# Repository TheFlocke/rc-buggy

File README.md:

# RC Rover 🌋 (WIP)

This project was developed as part of a high school competition organized by the German Aerospace Center (DLR). The challenge: design and build a rover capable of:
- 📊 Collecting sensor data
- 🧭 Navigating autonomously
- 🦾 Using a robotic arm to gather rock samples

To enable wireless control from any BLE-capable device, I developed:
- 💻 Custom microcontroller software
- 🌐 Dedicated web app
- 🖥️ Bespoke PCB design (unfortunately, the PCB was never manufactured due to supply issues)

The foundation for the code was a project from my teacher, which I significantly modified and expanded. While I focused on electronics/software ⚡️, my teammates handled mechanical engineering ⚙️.

## Project Screenshots 📸

## Installation ⚙️
### 🔌 Flash mcu-sw onto the ESP32
#### 1. 📋 Install Prerequisites
You’ll need VS Code or CLion with the PlatformIO extension.  
See the Links section below for tutorials.

#### 2. 💾 Download the Project
Clone or download this repository and open it in your chosen IDE.

#### 3. 🆔 Generate New UUIDs
1. Open `ESP32ble.h`  
2. Visit [uuidgenerator.net](https://www.uuidgenerator.net/)  
3. Generate new UUIDs and replace existing ones

#### 4. ⚡ Flash the ESP32
Upload the code to your ESP32 device.

#### 5. 📶 Test BLE Communication
Use nRF Connect or similar BLE apps to verify data transmission.

## Acknowledgements 🙏
- 👨‍🏫 [RC Car Project by my Teacher](https://github.com/bkZuendorf/rc-car)
- 🖨️ [3D-Printable Parts Repository](https://github.com/matiassingers/awesome-readme)

## Authors 👥
- [@TheFlocke](https://github.com/TheFlocke) 👤
- [@xNiicki](https://github.com/xNiicki) 👤

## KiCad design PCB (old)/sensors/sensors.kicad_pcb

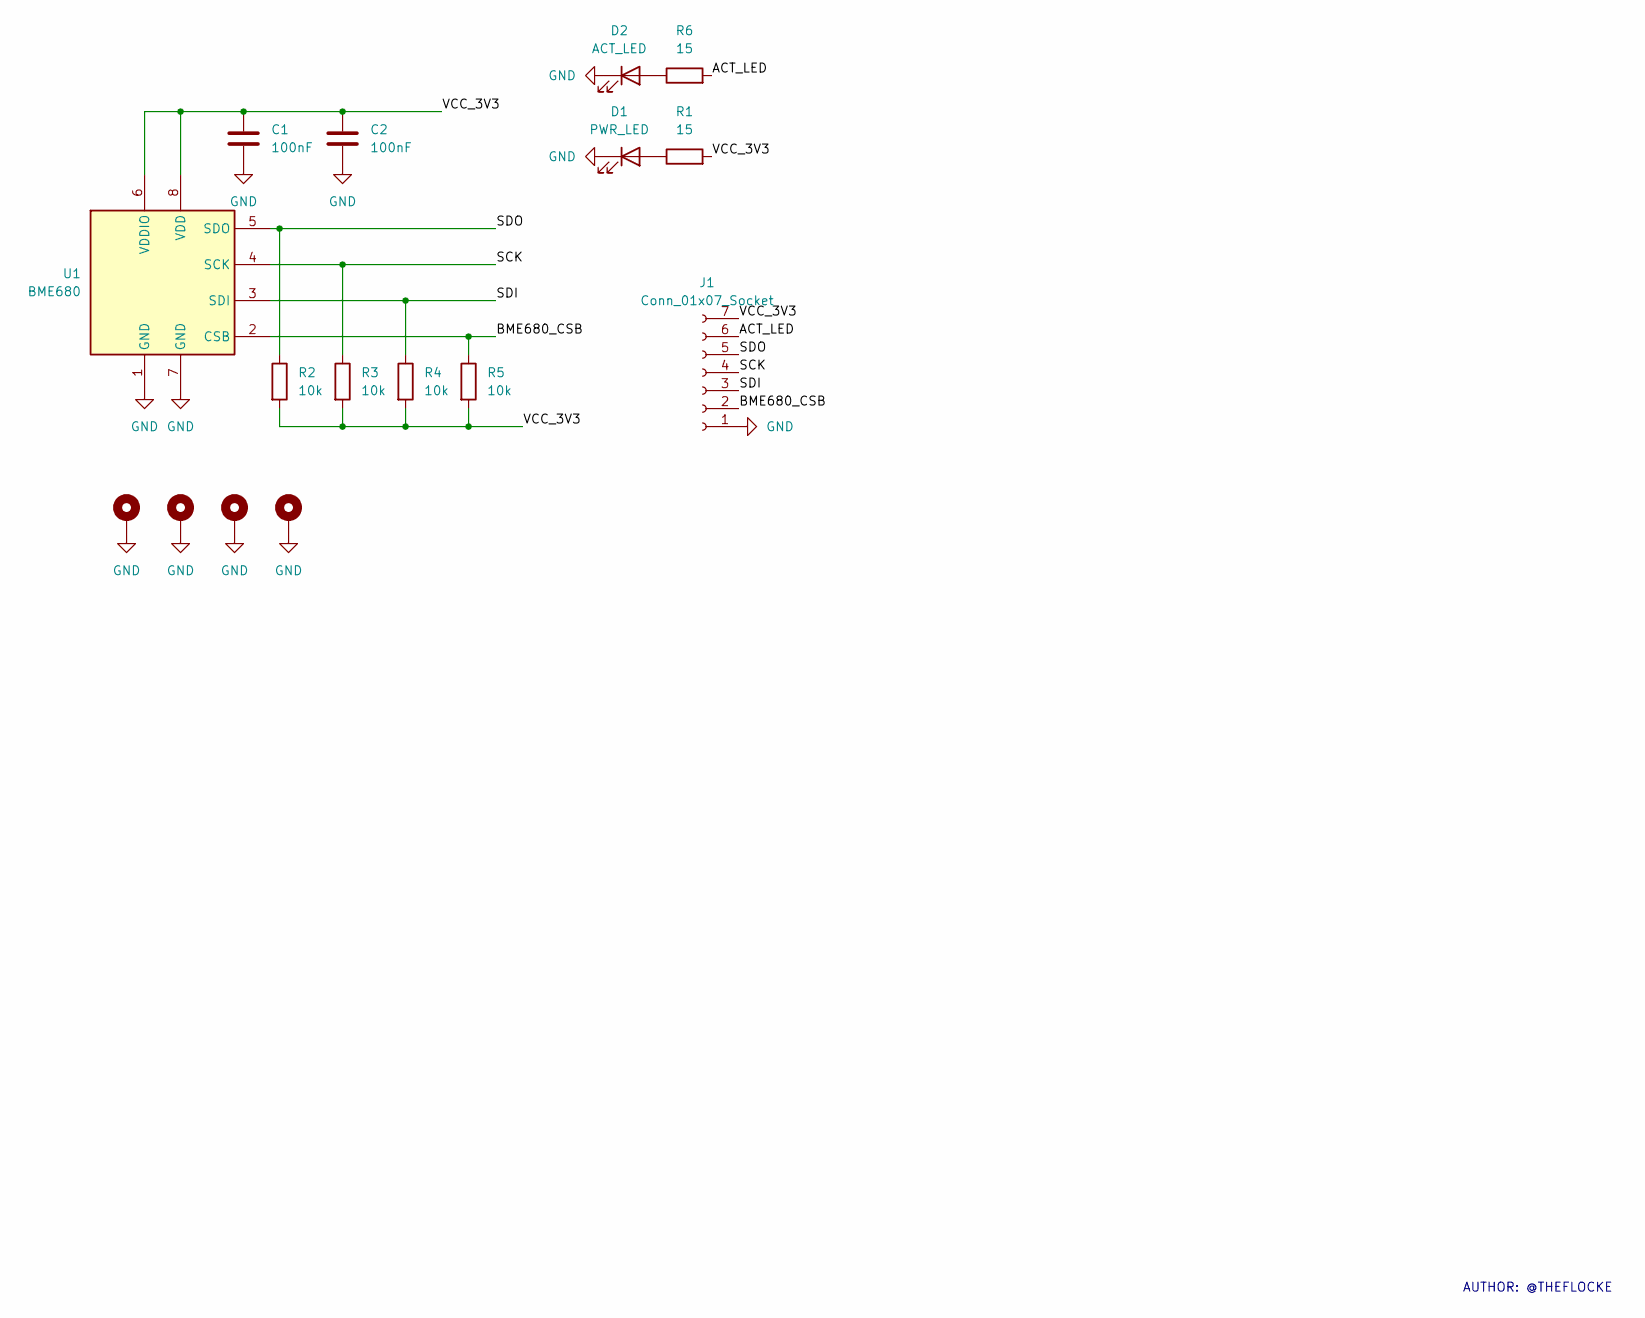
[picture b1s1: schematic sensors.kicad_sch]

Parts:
C1, C2: 100nF; C_0805_2012Metric_Pad1.18x1.45mm_HandSolder
D1: PWR_LED; C_0805_2012Metric_Pad1.18x1.45mm_HandSolder
D2: ACT_LED; C_0805_2012Metric_Pad1.18x1.45mm_HandSolder
H1, H2, H3, H4: MountingHole_Pad; MountingHole_3.2mm_M3_DIN965_Pad_TopBottom
J1: Conn_01x07_Socket; JST_EH_B7B-EH-A_1x07_P2.50mm_Vertical
R1, R6: 15; R_0805_2012Metric_Pad1.20x1.40mm_HandSolder
R2, R3, R4, R5: 10k; R_0805_2012Metric_Pad1.20x1.40mm_HandSolder
U1: BME680; Bosch_LGA-8_3x3mm_P0.8mm_ClockwisePinNumbering

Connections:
/ACT_LED: J1.6, R6.2
/BME680_CSB: J1.2, R5.1, U1.2 (CSB)
/SCK: J1.4, R3.1, U1.4 (SCK)
/SDI: J1.3, R4.1, U1.3 (SDI)
/SDO: J1.5, R2.1, U1.5 (SDO)
/VCC_3V3: C1.1, C2.1, J1.7, R1.2, R2.2, R3.2, R4.2, R5.2, U1.6 (VDDIO), U1.8 (VDD)
GND: C1.2, C2.2, D1.1 (K), D2.1 (K), H1.1, H2.1, H3.1, H4.1, J1.1, U1.1 (GND), U1.7 (GND)
unnamed: D1.2 (A), R1.1
unnamed: D2.2 (A), R6.1

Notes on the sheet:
AUTHOR: @THEFLOCKE

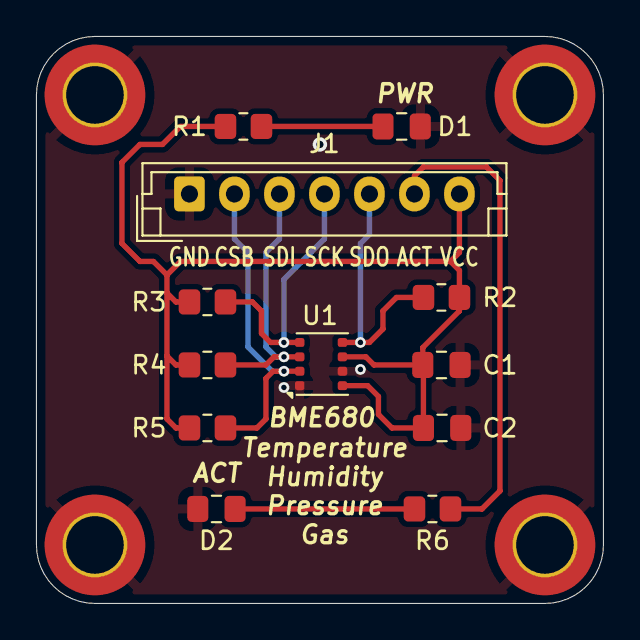
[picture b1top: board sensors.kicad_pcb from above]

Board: 2 copper layers, 31.5 x 31.5 mm, 16 parts (0 on the bottom side), 9 nets.

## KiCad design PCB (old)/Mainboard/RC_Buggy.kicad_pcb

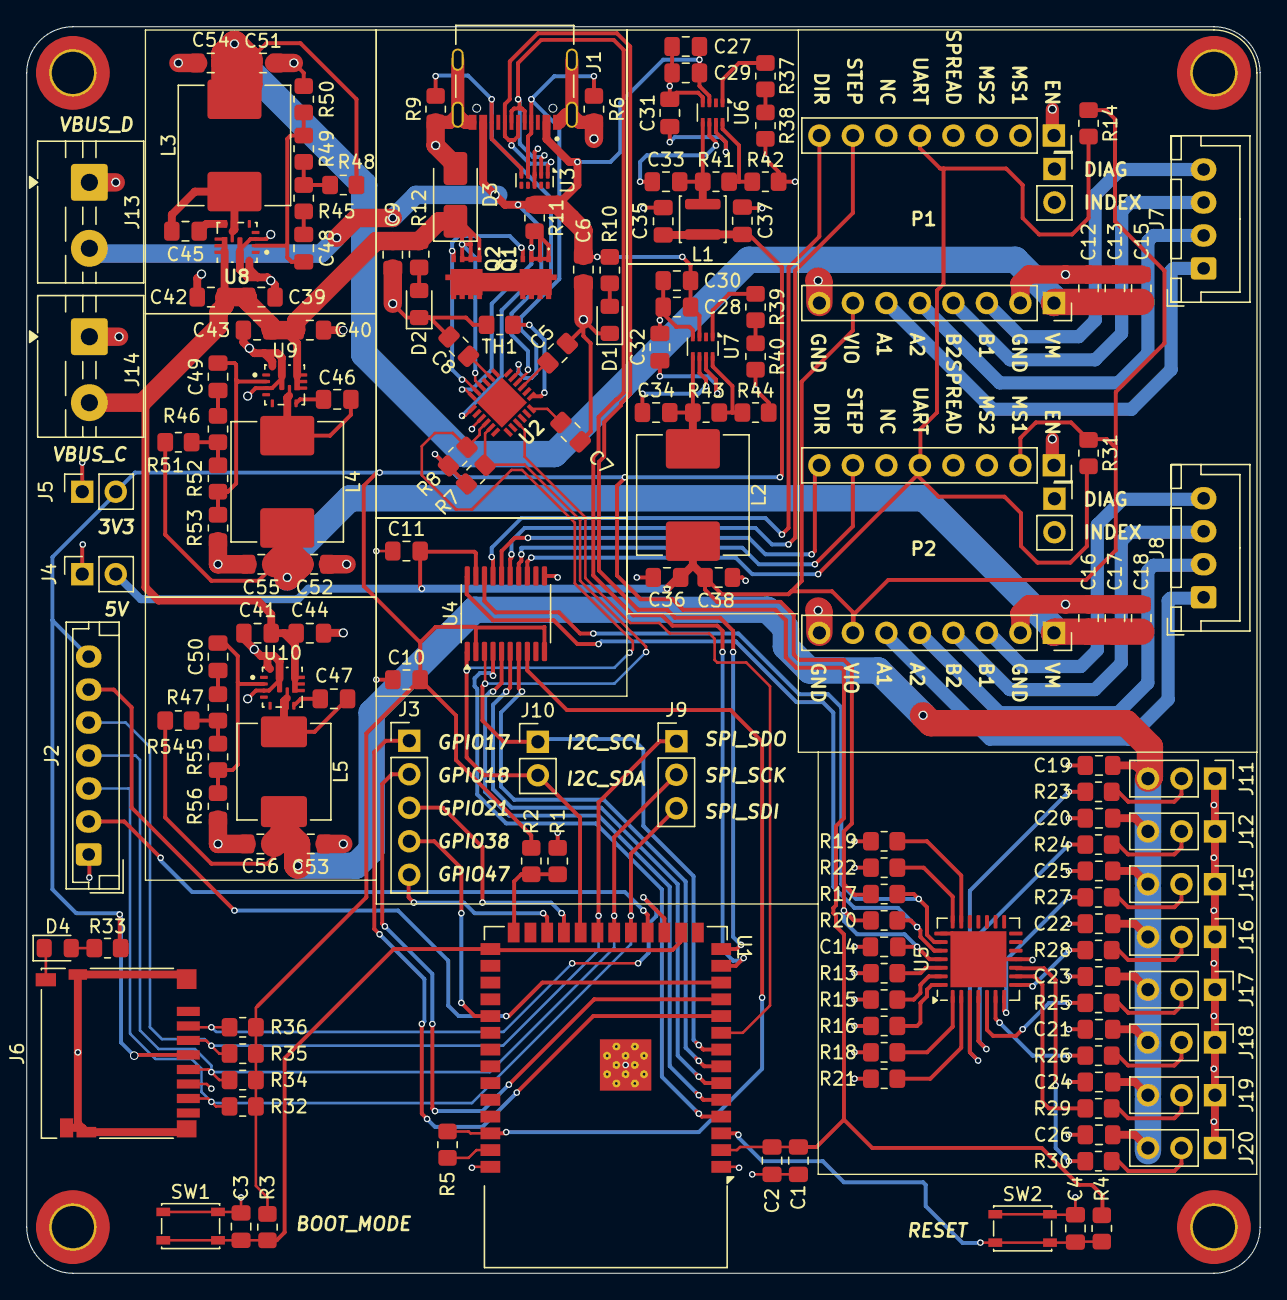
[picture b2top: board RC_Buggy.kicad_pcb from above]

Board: 4 copper layers, 93.5 x 94.5 mm, 162 parts (0 on the bottom side), 111 nets.

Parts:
C1, C3, C4, C10, C11, C45, C46, C47: 0u1F; C_0805_2012Metric_Pad1.18x1.45mm_HandSolder
C2, C6, C9, C14, C27, C28, C29, C30, C39, C40, C41, C42, C43, C44: 10uF; C_0805_2012Metric_Pad1.18x1.45mm_HandSolder
C5, C7, C13, C15, C17, C18, C19, C20, C21, C22, C23, C24, C25, C26, C33, C34: 100nF; C_0805_2012Metric_Pad1.18x1.45mm_HandSolder
C8: 1uF; C_0805_2012Metric_Pad1.18x1.45mm_HandSolder
C12, C16: 100uF; C_0805_2012Metric_Pad1.18x1.45mm_HandSolder
C31, C32: 33nF; C_0805_2012Metric_Pad1.18x1.45mm_HandSolder
C35, C36, C37, C38, C51, C52, C53, C54, C55, C56: 22uF; C_0805_2012Metric_Pad1.18x1.45mm_HandSolder
C48, C49, C50: 100pF; C_0805_2012Metric_Pad1.18x1.45mm_HandSolder
D1, D2, D4: LED; D_0805_2012Metric_Pad1.15x1.40mm_HandSolder
D3: 100V; D_SMA
H1, H2, H3, H4: MountingHole_Pad; MountingHole_3.2mm_M3_DIN965_Pad_TopBottom
J1: TYPE-C-31-M-12; HRO_TYPE-C-31-M-12
J2: BME680; JST_EH_B7B-EH-A_1x07_P2.50mm_Vertical
J3: GPIO; PinHeader_1x05_P2.54mm_Vertical
J4: PW_5V; PinSocket_1x02_P2.54mm_Vertical
J5: PW_3V3; PinSocket_1x02_P2.54mm_Vertical
J6: Micro_SD_Card_Det_Hirose_DM3AT; microSD_HC_Hirose_DM3D-SF
J7: Stepper_1; JST_XH_B4B-XH-A_1x04_P2.50mm_Vertical
J8: Stepper_2; JST_XH_B4B-XH-A_1x04_P2.50mm_Vertical
J9: SPI; PinHeader_1x03_P2.54mm_Vertical
J10: I2C; PinHeader_1x02_P2.54mm_Vertical
J11: Servo 0; PinHeader_1x03_P2.54mm_Vertical
J12: Servo 1; PinHeader_1x03_P2.54mm_Vertical
J13, J14: PW_IO_bak; TerminalBlock_MaiXu_MX126-5.0-02P_1x02_P5.00mm
J15: Servo 4; PinHeader_1x03_P2.54mm_Vertical
J16: Servo 5; PinHeader_1x03_P2.54mm_Vertical
J17: Servo 2; PinHeader_1x03_P2.54mm_Vertical
J18: Servo 3; PinHeader_1x03_P2.54mm_Vertical
J19: Servo 6; PinHeader_1x03_P2.54mm_Vertical
J20: Servo 7; PinHeader_1x03_P2.54mm_Vertical
L1: 2u4H; L_APV_ANR3015
L2, L3, L4: 3u3H; L_APV_APH0850
L5: 4u3H; L_APV_APH0650
P1, P2: TMC2209_Socket
Q1, Q2: AON7262E
R1, R2, R3, R4, R10, R12, R13, R14, R15, R16, R17, R18, R19, R20, R21, R22, R31, R32, R34, R35, R36, R37, R38, R39, R40, R42, R44, R50, R53, R56: 10k; R_0805_2012Metric_Pad1.20x1.40mm_HandSolder
R5: 1k; R_0805_2012Metric_Pad1.20x1.40mm_HandSolder
R6, R7, R8, R9: 5k1; R_0805_2012Metric_Pad1.20x1.40mm_HandSolder
R11: 10m; R_0805_2012Metric_Pad1.20x1.40mm_HandSolder
R23, R24, R25, R26, R27, R28, R29, R30: 220; R_0805_2012Metric_Pad1.20x1.40mm_HandSolder
R33: 15; R_0805_2012Metric_Pad1.20x1.40mm_HandSolder
R41: 31k6; R_0805_2012Metric_Pad1.20x1.40mm_HandSolder
R43: 52k3; R_0805_2012Metric_Pad1.20x1.40mm_HandSolder
R45, R46, R47: 20k; R_0805_2012Metric_Pad1.20x1.40mm_HandSolder
R48, R51, R54: 49k9; R_0805_2012Metric_Pad1.20x1.40mm_HandSolder
R49, R52: 73k2; R_0805_2012Metric_Pad1.20x1.40mm_HandSolder
R55: 100k; R_0805_2012Metric_Pad1.20x1.40mm_HandSolder
SW1, SW2: SW_Push; SW_SPST_PTS810
TH1: NTC-10k; R_0805_2012Metric_Pad1.20x1.40mm_HandSolder
U1: ESP32-S3-WROOM-1
U2: AP33772
U3: TPD4E05U06DQA; USON-10_2.5x1.0mm_P0.5mm
U4: TXS0108EPW; TSSOP-20_4.4x6.5mm_P0.65mm
U5: PCA9685BS; QFN-28-1EP_6x6mm_P0.65mm_EP4.25x4.25mm
U6, U7: TPS62933; SOT-583-8
U8, U9, U10: TPS56637RPAR; CONV_TPS56637RPAR

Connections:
/ACT_LED: J2.6, U1.12 (IO8)
/BME680_CSB: J2.2, U1.18 (IO10)
/BOOT_Mode: C3.1, R3.2, SW1.2, U1.16 (IO46), U1.27 (IO0)
/CHIP_PU: C4.1, R4.2, SW2.2, U1.3 (EN)
/Connections/PWM0: J11.2, R23.2
/Connections/PWM1: J12.2, R24.2
/Connections/PWM2: J17.2, R25.2
/Connections/PWM3: J18.2, R26.2
/Connections/PWM4: J15.2, R27.2
/Connections/PWM5: J16.2, R28.2
/Connections/PWM6: J19.2, R29.2
/Connections/PWM7: J20.2, R30.2
/Connections/STEP1_A1: J7.1, P1.14 (B1)
/Connections/STEP1_A2: J7.2, P1.13 (A1)
/Connections/STEP1_B1: J7.4, P1.11 (B2)
/Connections/STEP1_B2: J7.3, P1.12 (A2)
/Connections/STEP2_A1: J8.1, P2.14 (B1)
/Connections/STEP2_A2: J8.2, P2.13 (A1)
/Connections/STEP2_B1: J8.4, P2.11 (B2)
/Connections/STEP2_B2: J8.3, P2.12 (A2)
/GPIO17: J3.1, U1.10 (IO17)
/GPIO18: J3.2, U1.11 (IO18)
/GPIO21: J3.3, U1.23 (IO21)
/GPIO38: J3.4, U1.31 (IO38)
/GPIO47: J3.5, U1.24 (IO47)
/I2C_SCL: J10.1, R7.1, U1.8 (IO15), U2.5 (SCL), U4.3 (A2)
/I2C_SDA: J10.2, R8.1, U1.22 (IO14), U2.4 (SDA), U4.1 (A1)
/Logic Level Converter/DATA0_5V: R20.1, U4.20 (B1), U5.24 (SDA)
/Logic Level Converter/DATA1_5V: R17.2, U4.18 (B2), U5.23 (SCL)
/Logic Level Converter/DATA2_5V: P1.8 (DIR), U4.17 (B3)
/Logic Level Converter/DATA3_5V: P2.8 (DIR), U4.16 (B4)
/Logic Level Converter/DATA4_5V: P1.7 (STEP), U4.15 (B5)
/Logic Level Converter/DATA5_5V: P2.7 (STEP), U4.14 (B6)
/Logic Level Converter/DATA6_5V: P1.5 (UART), P2.5 (UART), R14.2, R31.2, U4.13 (B7)
/PD_INT: U1.9 (IO16), U2.9 (GPIO3)
/SD_CSB: J6.2 (DAT3/CD), R36.1, U1.17 (IO9)
/SPI_SCK: J2.4, J6.5 (CLK), J9.2, R34.1, U1.20 (IO12)
/SPI_SDI: J2.3, J6.7 (DAT0), J9.3, R32.1, U1.19 (IO11)
/SPI_SDO: J2.5, J6.3 (CMD), J9.1, R35.1, U1.21 (IO13)
/STEP1_DIR: U1.4 (IO4), U4.4 (A3)
/STEP1_STEP: U1.6 (IO6), U4.6 (A5)
/STEP2_DIR: U1.5 (IO5), U4.5 (A4)
/STEP2_STEP: U1.7 (IO7), U4.7 (A6)
/UART_RX: R5.1, U1.38 (IO2), U4.8 (A7)
/UART_TX: R5.2, U1.39 (IO1)
/USB-C/CC1: J1.A5 (CC1), R6.2, U2.17 (CC1), U3.4 (D2+)
/USB-C/CC2: J1.B5 (CC2), R9.2, U2.16 (CC2), U3.5 (D2-)
/USB-C/PWR_EN: Q1.4 (G), Q2.4 (G), U2.23 (PWR_EN)
/USB-C/VCC: Q1.1 (S_1), Q1.2 (S_2), Q1.3 (S_3), R11.2, U2.24 (VCC)
/USB_D+: J1.A6 (DP1), J1.B6 (DP2), U1.14 (USB_D+), U3.1 (D1+)
/USB_D-: J1.A7 (DN1), J1.B7 (DN2), U1.13 (USB_D-), U3.2 (D1-)
GND: C1.2, C2.2, C3.2, C4.2, C5.2, C6.2, C7.2, C8.2, C9.2, C10.1, C11.1, C12.2, C13.1, C14.1, C15.1, C16.2, C17.1, C18.1, C19.2, C20.2, C21.2, C22.2, C23.2, C24.2, C25.2, C26.2, C27.2, C28.2, C29.2, C30.2, C31.2, C32.2, C35.2, C36.2, C37.2, C38.2, C39.2, C40.2, C41.2, C42.2, C43.2, C44.2, C51.2, C52.2, C53.2, C54.2, C55.2, C56.2, D1.1 (K), D2.1 (K), D3.2 (A), H1.1, H2.1, H3.1, H4.1, J1.A1_B12 (GND), J1.B1_A12 (GND), J1.S1 (SHIELD), J1.S2 (SHIELD), J1.S3 (SHIELD), J1.S4 (SHIELD), J2.1, J4.1, J5.1, J6.6 (VSS), J6.9 (DET_B), J6.11 (SHIELD), J11.1, J12.1, J13.1, J14.1, J15.1, J16.1, J17.1, J18.1, J19.1, J20.1, P1.1 (EN), P1.10 (GND), P1.16 (GND), P2.1 (EN), P2.10 (GND), P2.16 (GND), R1.2, R6.1, R9.1, R13.2, R15.2, R16.2, R18.2, R19.1, R21.2, R22.2, R38.2, R40.2, R42.2, R44.2, R50.2, R53.2, R56.2, SW1.1, SW2.1, TH1.2, U1.1 (GND), U1.40 (GND), U1.41 (GND), U2.3 (GND), U3.3 (GND), U3.8 (GND), U4.11 (GND), U5.11 (VSS), U5.22 (EXTCLK), U5.29 (VSS), U6.4 (GND), U7.4 (GND), U8.3 (AGND), U8.9 (PGND), U8.10 (MODE), U9.3 (AGND), U9.9 (PGND), U9.10 (MODE), U10.3 (AGND), U10.9 (PGND), U10.10 (MODE)
unnamed: C48.1, R45.1
unnamed: C49.1, R46.1
unnamed: C50.1, R47.1
unnamed: D1.2 (A), R10.1
unnamed: D2.2 (A), R12.1
unnamed: D4.2 (A), R33.1
unnamed: D4.1 (K), J6.10 (DET_A)
unnamed: Q1.5 (D_1), Q1.6 (D_2), Q1.7 (D_3), Q1.8 (D_4), Q1.9 (D_5), Q1.10 (D_6), Q1.11 (D_7), Q2.5 (D_1), Q2.6 (D_2), Q2.7 (D_3), Q2.8 (D_4), Q2.9 (D_5), Q2.10 (D_6), Q2.11 (D_7)
unnamed: R37.2, R38.1
unnamed: R39.2, R40.1
unnamed: R45.2, R48.2, R49.1
unnamed: R46.2, R51.2, R52.1
unnamed: R47.2, R54.2, R55.1
unnamed: R1.1, R2.1, U1.26 (IO45)
unnamed: C5.1, U2.15 (IFB)
unnamed: TH1.1, U2.13 (OTP)
unnamed: C7.1, U2.12 (V3VD)
unnamed: C8.1, U2.20 (V5V)
unnamed: R13.1, U5.26 (A0)
unnamed: R15.1, U5.27 (A1)
unnamed: R16.1, U5.28 (A2)
unnamed: R18.1, U5.1 (A3)
unnamed: R21.1, U5.2 (A4)
unnamed: R22.1, U5.21 (A5)
unnamed: R23.1, U5.3 (LED0)
unnamed: R24.1, U5.4 (LED1)
unnamed: R25.1, U5.5 (LED2)
unnamed: R26.1, U5.6 (LED3)
unnamed: R27.1, U5.7 (LED4)
unnamed: R28.1, U5.8 (LED5)
unnamed: R29.1, U5.9 (LED6)
unnamed: R30.1, U5.10 (LED7)
unnamed: R19.2, U5.20 (~OE)
unnamed: C33.1, U6.6 (BST)
unnamed: R41.2, R42.1, U6.8 (FB)
unnamed: R37.1, U6.1 (RT)
unnamed: C31.1, U6.7 (SS)
unnamed: C33.2, L1.1, R41.1, U6.5 (SW)
unnamed: C34.1, U7.6 (BST)
unnamed: R43.2, R44.1, U7.8 (FB)
unnamed: R39.1, U7.1 (RT)
unnamed: C32.1, U7.7 (SS)
unnamed: C34.2, L2.1, R43.1, U7.5 (SW)
unnamed: C45.2, U8.7 (BOOT)
unnamed: C48.2, R49.2, R50.1, U8.2 (FB)
unnamed: C45.1, L3.1, U8.6 (SW)
unnamed: C46.2, U9.7 (BOOT)
unnamed: C49.2, R52.2, R53.1, U9.2 (FB)
unnamed: C46.1, L4.1, U9.6 (SW)
unnamed: C47.2, U10.7 (BOOT)
unnamed: C50.2, R55.2, R56.1, U10.2 (FB)
unnamed: C47.1, L5.1, U10.6 (SW)
VBUS_C: C9.1, C39.1, C40.1, C41.1, C42.1, C43.1, C44.1, D3.1 (K), J14.2, Q2.1 (S_1), Q2.2 (S_2), Q2.3 (S_3), R12.2, U2.22 (VBUS), U8.8 (VIN), U9.8 (VIN), U10.8 (VIN)
VBUS_D: C6.1, C27.1, C28.1, C29.1, C30.1, J1.A4_B9 (VBUS), J1.B4_A9 (VBUS), J13.2, R10.2, R11.1, U2.1 (ISENP), U6.3 (VIN), U7.3 (VIN)
VCC_3V3: C1.1, C2.1, C10.2, C35.1, C37.1, J2.7, J5.2, J6.4 (VDD), L1.2, R2.2, R3.1, R4.1, R7.2, R8.2, R32.2, R33.2, R34.2, R35.2, R36.2, U1.2 (3V3), U4.2 (VCCA), U4.10 (OE)
VCC_5V: C11.2, C14.2, C36.1, C38.1, J4.2, L2.2, P1.15 (VIO), P2.2 (MS1), P2.15 (VIO), R14.1, R17.1, R20.2, R31.1, U4.19 (VCCB), U5.25 (VDD)
VCC_Servo: C19.1, C20.1, C21.1, C22.1, C23.1, C24.1, C25.1, C26.1, C53.1, C56.1, J11.3, J12.3, J15.3, J16.3, J17.3, J18.3, J19.3, J20.3, L5.2, R54.1
V_MOT_0: C12.1, C13.2, C15.2, C51.1, C54.1, L3.2, P1.9 (VM), R48.1
V_MOT_1: C16.1, C17.2, C18.2, C52.1, C55.1, L4.2, P2.9 (VM), R51.1

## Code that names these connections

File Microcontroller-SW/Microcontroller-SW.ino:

#include <crbk_ble.h>
#include "TMC2209.h"
#include "crbk_servo.h"

const int ACT_LED = 8; // Activitiy LED for the Sensor PCB
const int SD_CSB = 9;
const int BME680_CSB = 10;
const int SPI_SDI = 11;
const int SPI_SCK = 12;
const int SPI_SDO = 13;
const int I2C_SDA = 14;
const int I2C_SCL = 15;
const int PD_INT = 16;
// GPIO Ports used to control the TMC2209
const int UART_TX = 1;
const int UART_RX = 2;
const int STEP1_DIR = 4;
const int STEP2_DIR  = 5;
const int STEP1_STEP = 6;
const int STEP2_STEP = 7;
// GPIO Ports that are not reserved by any devices
const int GPIO_17 = 17;
const int GPIO_18 = 18;
const int GPIO_21 = 21;
const int GPIO_38 = 38;
const int GPIO_47 = 47;
const int GPIO_48 = 48;

// initializing motorrdriver(s)
// Important: For NEMA 17 motors, the current is in general in the range of 0.5A to 0.8A RMS, which is a reference voltage (Vref) of 0.7V to 1.1V.
TMC2209 stepper_driver_left;
const TMC2209::SerialAddress SERIAL_ADDRESS_left = TMC2209::SERIAL_ADDRESS_left; // defining Serial address assigned by the library as a constant
TMC2209 stepper_driver_right;
const TMC2209::SerialAddress SERIAL_ADDRESS_right = TMC2209::SERIAL_ADDRESS_right; // defining Serial address assigned by the library as a constant
const uint8_t REPLY_DELAY = 4;
const long SERIAL_BAUD_RATE = 115200;


void setup() {
// setting up serial connection for communication with motordriver(s)
  stepper_driver_left.setup(Serial1,SERIAL_BAUD_RATE,SERIAL_ADDRESS_left,UART_RX,UART_TX);
  stepper_driver_left.setReplyDelay(REPLY_DELAY);
  stepper_driver_right.setup(Serial1,SERIAL_BAUD_RATE,SERIAL_ADDRESS_right,UART_RX,UART_TX);
  stepper_driver_right.setReplyDelay(REPLY_DELAY);
// Setting pinMode for for motor-control
  pinMode(STEP1_DIR, OUTPUT);
  pinMode(STEP2_DIR, OUTPUT);
  pinMode(STEP1_STEP, OUTPUT);
  pinMode(STEP2_STEP, OUTPUT);
}

void loop() { 
  crbkRCCarBLE.handle();
  int speed = crbkRCCarBLE.getSpeed();
  int left  = abs(speed);
  int right = abs(speed);
  int direction = crbkRCCarBLE.getDirection();
  if(direction<0) {
    // reduziere Geschwindigkeit nach links
    left -= left*(-direction/90.0);
  } else if(direction>0) {
    // reduziere Geschwindigkeit nach rechts
    right -= right*(direction/90.0);
  }
  if(speed>0) {
    // forward
    analogWrite(STEP1_STEP, left);
    digitalWrite(STEP1_DIR, LOW);

    analogWrite(STEP2_STEP, right);
    digitalWrite(STEP2_DIR, LOW);
  } else if(speed<0) {
    // backward
    analogWrite(STEP1_STEP, left);
    digitalWrite(STEP1_DIR, HIGH);

    analogWrite(STEP2_STEP, right);
    digitalWrite(STEP2_DIR, HIGH);
  } else {
    // stop (so they aren't left floating)
    digitalWrite(STEP1_STEP, LOW);
    digitalWrite(STEP1_DIR, LOW);

    digitalWrite(STEP2_STEP, LOW);
    digitalWrite(STEP2_DIR, LOW);
  }
}

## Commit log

2025-01-16 Delete 3D-Design directory
    Wird nicht gebraucht, da wir ein komplettes neu Design für den RC-Buggy erstellen müssen
2025-04-21 Uploading existing files
2025-04-21 Adding files based on the Project of bkzuendorf
2025-04-21 Pinout change.
2025-04-21 Changed Pinout according to PCB
2025-04-21 Add Fontsawsome.
2025-04-21 Add speed slider.
2025-04-21 add .gitignore.
2025-04-21 Changed Setup for TMC2209
2025-04-22 Added pinMode
2025-04-22 Added STEP and DIR
2025-04-22 Fixed Spacing
2025-04-22 Using PlatformIO
2025-04-22 Hopefully my ide works
2025-04-22 IDE changes
2025-04-22 IDE fixes
2025-04-23 Some changes
2025-04-23 Update Project structure.
2025-04-23 Fix micro errors.
2025-04-23 Update JS.
2025-04-23 Three.js doku
2025-04-23 Add Three.js
2025-04-23 Add 3d Models.
2025-04-23 Add NPM/Three.js
2025-04-23 Remove Three.JS (THIS SHIT IS NOT FOR MY BRAIN I HATE 3D MODELS I WILL NEVER WORK WITH THAT SHIT AGAIN).
2025-04-23 Added new Characterristics and reformated the code
2025-04-23 Added new ARM_STATE
2025-04-23 Reformated
2025-04-23 Add Rotated Arm.
2025-04-23 added Arm controls
2025-04-23 added Sensor get command
2025-04-23 Make arms draggable.
2025-04-23 Changed Limits for ARM
2025-04-23 Added Reading Command send over BLE
2025-04-23 Fixed Wrong UUID for STATE_CMD
2025-04-23 Added Comment
2025-04-24 Fixing Rotation.
2025-04-24 added Wheel and Speed Control
2025-04-24 Base files for Servo
2025-04-24 Kinde fix movement.
2025-04-24 Added Characteristics.
2025-04-24 Added Characteristics listener.
2025-04-24 Add Infos.
2025-04-24 New?
2025-04-24 Servo function is now defined and minor fix for ble
2025-04-24 Fixed.
2025-04-24 Add toggle function.
2025-04-24 Fix armController.
2025-04-24 Fix Styling.
2025-04-24 Line breaks.
2025-04-24 Style fixes.
2025-04-24 Remove console.log.
2025-04-24 Fixed Styles.
2025-04-24 Add touchscreen support.
2025-04-24 Fix border.
2025-04-24 Rearrange circles.
2025-04-24 Fixing height.
2025-04-24 removed unused.
2025-04-24 Add stats.
2025-04-24 Add history + dumps.
2025-04-24 fix ble
2025-04-24 Update speedInput.
2025-04-24 Add History.
2025-04-24 Update History.
2025-04-24 BLE FIXED!!!
2025-04-24 Add Wheels.
2025-04-24 Added setup, read and get Command
2025-04-25 Added Servo and Sensor Updates and funtions. Servo is now controllable by BLE Client
2025-04-25 Fix Bluetooth.
2025-04-25 Update HTML.
2025-04-25 BugFix.
2025-04-25 fixed Cmd Characteristics
2025-04-25 remove console.log
2025-04-25 Edit dot size.
2025-04-25 Edit small.
2025-04-28 Working Stepper function
2025-04-28 Working Stepper function with servo
2025-04-28 Final Stepper
2025-04-28 Final Stepper FINAL
2025-04-29 Final Stepper FINAL 1
2025-04-29 Final Changes
2025-04-29 Fixed Grammar
2025-04-29 Fixed Author
2025-04-29 Fixed Typo
2025-05-05 Fixed Stepper
2025-05-10 Fixed Servo
2025-05-10 Typo
2025-05-12 Fixed BLE Send
2025-05-12 BLE fix for no delay and made changes for 2 inverted Servos
2025-05-12 Deleted an NOTIFY as it is not used
2025-05-12 Minor fixes
2025-05-12 Changed Variable Name and deleted unused code
2025-05-12 Fixed Notify
2025-05-12 Made Timeout smaller so that the Slider is smoother
2025-05-12 Changed Logo, the filestructure and name
2025-05-12 cache fixes
2025-05-12 Name fix
2025-05-13 Fixed Servos
2025-05-13 Added half Service (need to do more work)
2025-05-13 Added Service Sensor with Characterstics and fix of Arm read
2025-05-13 added getSensor functions
2025-05-13 Build full Sensor function
2025-05-13 Added yield() function so programm is still usable while Sensor is doing its things
2025-05-13 fixed compiler thinking String is float
2025-05-13 fixed using same UUID for all Characteristic
2025-05-13 added Timeout
2025-05-14 fix delay caused by sensor read function
2025-05-14 Deleted Descriptors as they dont work and arent needed
2025-05-14 added asyncors function for sensor and changed Website for temp use
2025-05-14 Name fix added Sensor uuid
2025-05-14 rename of UUID var
2025-05-16 Name fixes
2025-05-26 Fixed Gas resistence
2025-05-29 fixes
2025-05-29 added both Services
2025-05-29 fixed the lagging behind
2025-05-29 fixed the bluetooth
2025-05-30 added Settings Page
2025-06-02 added safe area setting for first Wheel
2025-06-02 fixed naming and added the rest of the safe area values
2025-06-03 fixed decimal numbers
2025-06-04 looks
2025-06-09 swiched from adafruit to boschtec libary and also added two tasks for Sensor and BLE handleing
2025-06-10 photo
2025-06-13 added Tasks for BLE and Sensor
2025-06-13 added Mutex for I2C as tasks were created who dont know about eachother
2025-06-17 Some reconstruction so that the code woprks more efficent and faster
2025-06-18 updatet Stepper function for more efficency
2025-06-18 fixed formart
2025-06-19 added forgotten uuids
2025-06-19 removed unnescarry varaibles and updated to libary v2
2025-06-19 disabled Serial
2025-06-19 deleted daly as it is unnessary
2025-06-19 fixed checkINT function
2025-06-19 combined CMD and ARM and made new function -> ID:VALUE
2025-06-19 made SensorCallbacks more efficent
2025-06-19 upload images and deleted pcb new
2025-06-20 made sensor more efficent
2025-06-21 made code more efficent and faster for chars
2025-06-21 added new syntax for CMD send
2025-06-21 added translation to English
2025-06-23 made Vars more readable
2025-06-24 fixed some bugs
2025-06-27 disabled debugging functions
2025-06-27 fixed cache bug
2025-06-27 fixed Ble disconnect
2025-06-27 added sensor values to main page
2025-06-27 made sensor data look better and created identifiers
2025-06-27 new version
2025-06-27 final fixes
2025-06-27 verticals sliders design final
2025-07-01 updatet pinout for rover
2025-07-12 debug
2025-07-16 some changes for better debugging
2025-07-16 made debugging work
2025-07-16 fixed typos
2025-07-16 fixed hopefully all bugs
2025-07-16 set limits
2025-07-16 setting limits
2025-07-17 fixed id numbering
2025-07-17 pinout fix
2025-09-20 Initial plan
2025-09-20 Implement comprehensive mobile-friendly improvements for RCRover web interface
2025-09-20 Add comprehensive .github/copilot-instructions.md with validated commands and timing
